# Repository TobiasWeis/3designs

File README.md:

# 3designs
collection of different objects for 3d printing

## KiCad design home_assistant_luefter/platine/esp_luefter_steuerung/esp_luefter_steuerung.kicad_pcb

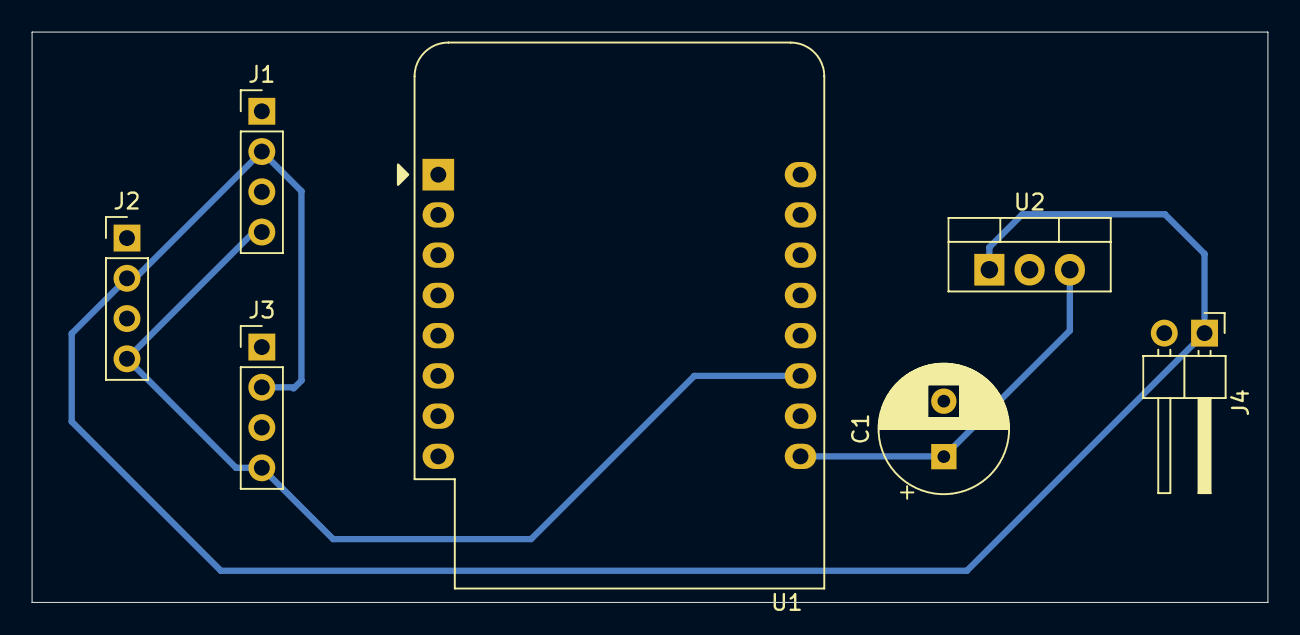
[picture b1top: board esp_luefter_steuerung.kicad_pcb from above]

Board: 2 copper layers, 78.0 x 36.0 mm, 7 parts (0 on the bottom side), 4 nets.

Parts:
C1: C_Polarized; CP_Radial_D8.0mm_P3.50mm
J1, J2, J3: Conn_01x04_Pin; PinHeader_1x04_P2.54mm_Vertical
J4: PWR Input 12V; PinHeader_1x02_P2.54mm_Horizontal
U1: WeMos_D1_mini; WEMOS_D1_mini_light
U2: LM7805_TO220; TO-220-3_Vertical

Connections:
+12V: J1.2, J2.2, J3.2, J4.1, U2.1 (VI)
GND: C1.2, J1.1, J2.1, J3.1, J4.2, U1.10 (GND), U2.2 (GND)
unnamed: J1.4, J2.4, J3.4, U1.11 (D4)
unnamed: C1.1, U1.9 (5V), U2.3 (VO)

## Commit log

2017-10-24 initial checkin
2017-10-26 improvements to tablet holder, added robot battery holder and skytree miniature mount
2017-10-29 added robot stand
2017-10-31 locker for rear battery holder to prevent battery from slipping out
2017-10-31 added robot bumper
2017-11-01 new bumper design using screws for easier printing
2017-11-01 finetuning of bumper design
2017-11-08 added monstar mount
2017-11-08 adapter monstar mount, fits perfectly now and seems to hold
2017-11-08 robot bumper...
2017-11-12 another bumper design
2017-11-12 added new mounts for robot bumper
2017-11-12 minor
2018-02-20 added cardholder and headphonebox
2018-02-27 added freecad propeller design
2018-02-28 ring
2018-03-03 added cr-10 closet plan
2018-03-05 added headphone-hool freecad model, minor in cr-10 closet design
2018-03-09 added pegboard hooks
2018-03-11 hooks for pine64 print monitor
2018-03-11 added C920 webcam-mount for fabminiv2
2018-03-11 minor changes
2018-03-19 led holder and update of case
2018-03-24 cr10 holder for control box
2018-03-24 top holder added
2018-03-26 parts for cr10
2018-03-26 added ledbar for cr10
2018-04-01 new version of spoolholder, cleaner
2018-05-06 added teleprompter
2018-05-12 added cameraslider files
2018-05-17 adjusted camera-slider files to real 25mm bars, some mechanical improvements
2018-05-23 added start of blender simulation
2018-12-09 added torque tester
2018-12-16 added camera-dolly
2018-12-30 added cnc pcb holder
2019-06-24 added schalter
2019-06-25 minor fixes
2019-06-26 more changes on lightswitch
2019-06-26 another little change, should be final version now
2019-06-28 another hue dimmer switch holder
2019-07-01 added tischfuesse
2019-07-15 added schirmhalter
2019-07-17 minor mods
2019-07-19 added another double switch adapter for hue
2019-07-31 added wallpixel shell
2019-10-08 added balcony-hooks for catbox
2019-10-08 added servo-holder for cat-laser-turret
2019-10-23 added holder for katzenrohr
2019-10-25 added rohrverbinder
2019-10-26 verbinder is nice now
2019-10-26 updated with correct radius
2019-10-26 corrected wallthickness to 1.2
2019-10-26 shorter
2019-10-26 added lattenhalterung
2021-10-30 changes to katzenstuff, added hexdisplay
2022-12-04 removed fingerprint checking, enabled https-insecure, added eve-2
2023-01-08 added kratzstangenhalterung
2023-11-27 added ecocount 3d model
2023-11-28 moved
2023-11-29 adjusted urls
2025-09-25 added latest 3designs
2025-09-25 added arm for lightholder
2025-09-26 added svg and cutout of skirtinboard
2025-09-26 added mirror holder
2025-09-29 added skadis hook
2025-09-29 refined skadis hook
2025-09-30 more skadis hooks
2025-10-01 more skadis
2025-10-04 WIP lightarm
2025-10-04 WIP light body
2025-10-05 WIP base
2025-11-18 added fanholder
2025-11-18 added esphome code for wemo d1
2025-11-19 added sketch for pcb
2025-11-19 increase trace widths
2025-11-20 added holder design files
